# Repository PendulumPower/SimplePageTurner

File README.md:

# SimplePageTurner
A simple BLE page-turner using an Xiao ESP32-S3
This project is my attempt at making a wireless page turner for musicians at a lower cost than buying one.<br>
It could also theoretically be used for other things, since the firmware can be modified<br>
Assembly:

Schematic:

PCB Design:

PCB Render:

<br><br>
Cost Breakdown:<br>
Parts listed in BOM + Shipping and Tariffs: $20<br>
PCB Costs with tax and shipping: $10<br>
Total: $30<br>
I would consider this a success for reaching my goal of making a cheaper page turner, since most are around $30, and this would be at least $10 cheaper due to the PCB, not even accounting for other components and shipping savings.

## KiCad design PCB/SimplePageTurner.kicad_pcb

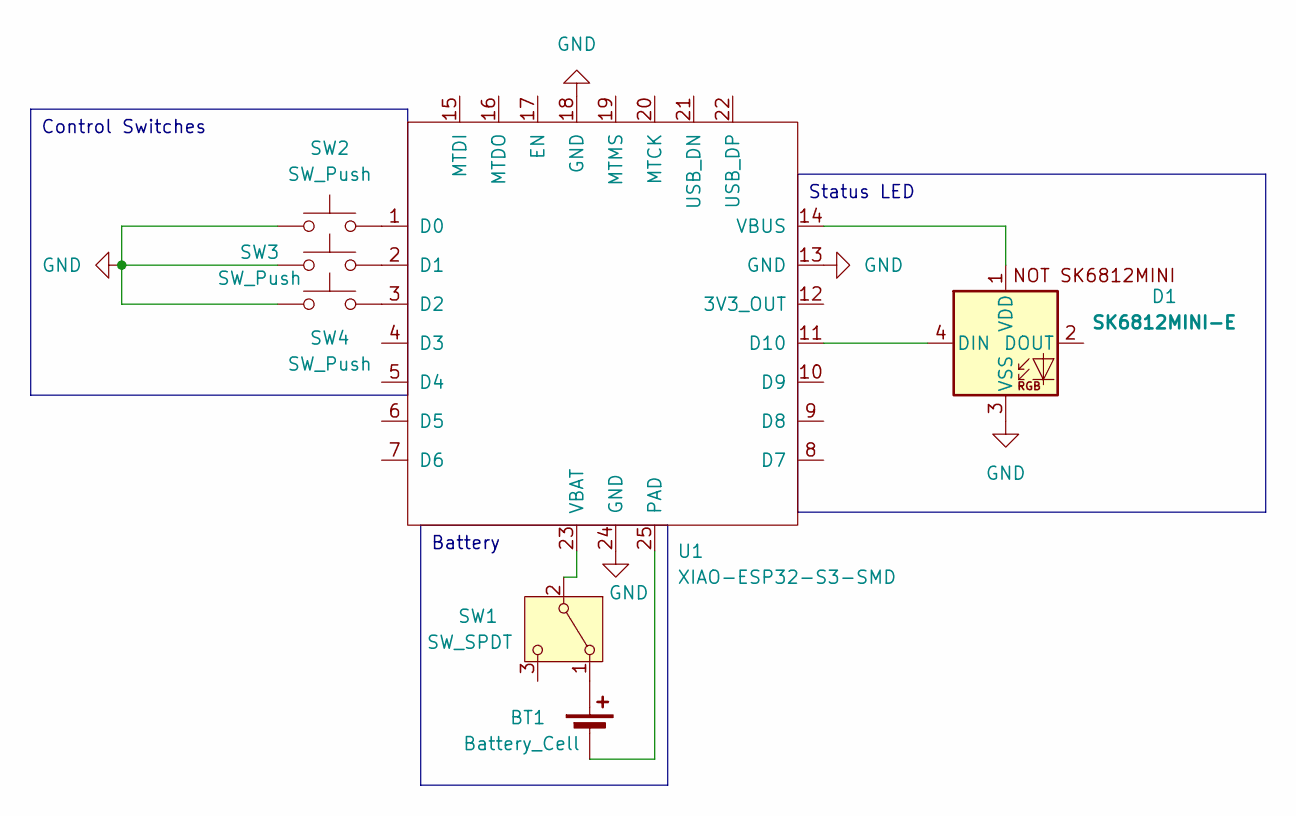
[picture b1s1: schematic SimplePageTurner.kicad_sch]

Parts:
BT1: Battery_Cell; JST_PH_S2B-PH-K_1x02_P2.00mm_Horizontal
D1: SK6812MINI-E; SK6812MINI-E_fixed
SW1: SW_SPDT; SW_Slide_SPDT_Straight_CK_OS102011MS2Q
SW2, SW3: SW_Push; SW_Cherry_MX_1.00u_PCB
SW4: SW_Push; SW_PUSH_6mm_H7.3mm
U1: XIAO-ESP32-S3-SMD

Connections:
GND: D1.3 (VSS), SW2.1, SW3.1, SW4.1, U1.13 (GND), U1.18 (GND), U1.24 (GND)
unnamed: BT1.1 (+), SW1.1 (A)
unnamed: BT1.2 (-), U1.25 (PAD)
unnamed: D1.4 (DIN), U1.11 (D10)
unnamed: D1.1 (VDD), U1.14 (VBUS)
unnamed: SW1.2 (B), U1.23 (VBAT)
unnamed: SW2.2, U1.1 (D0)
unnamed: SW3.2, U1.2 (D1)
unnamed: SW4.2, U1.3 (D2)

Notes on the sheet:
Battery
Status LED
Control Switches

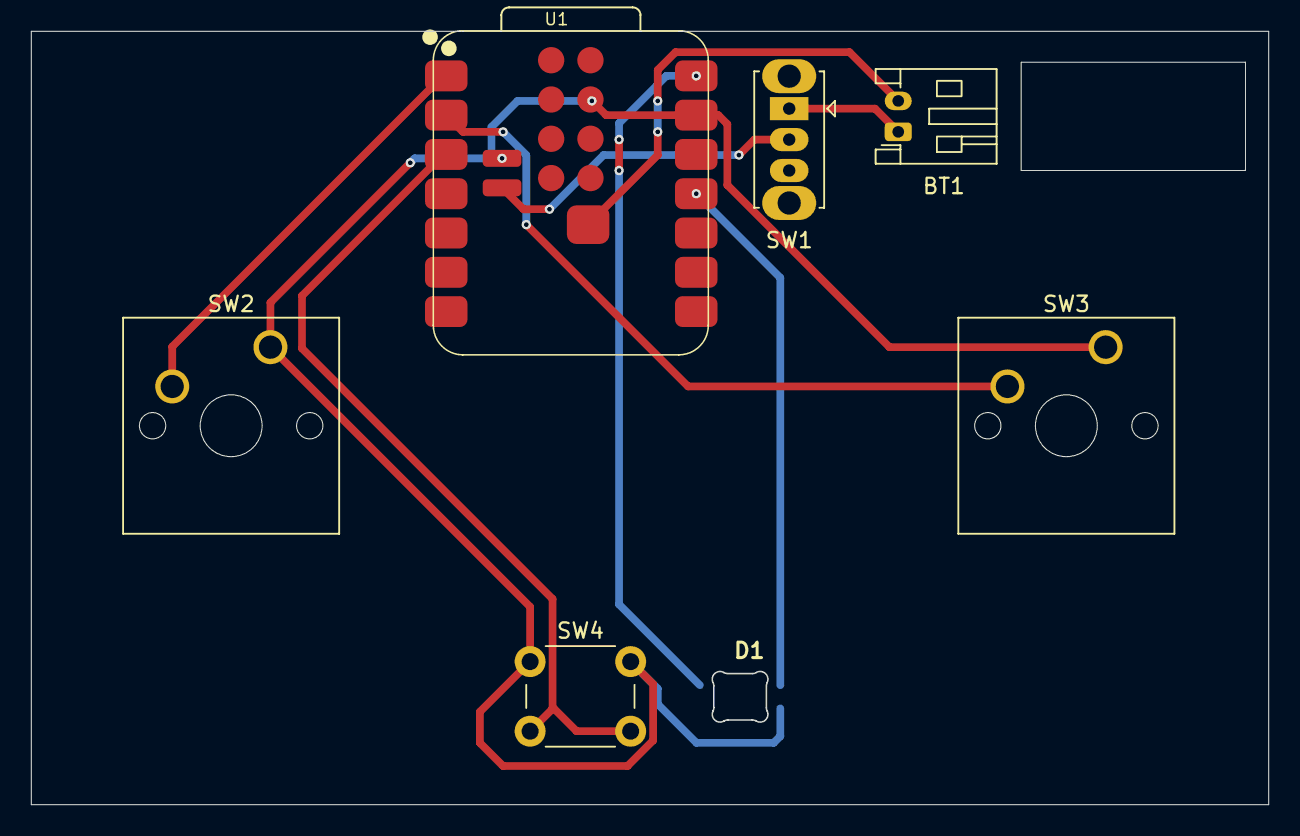
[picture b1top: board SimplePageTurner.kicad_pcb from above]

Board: 2 copper layers, 80.0 x 50.0 mm, 7 parts (0 on the bottom side), 9 nets.
